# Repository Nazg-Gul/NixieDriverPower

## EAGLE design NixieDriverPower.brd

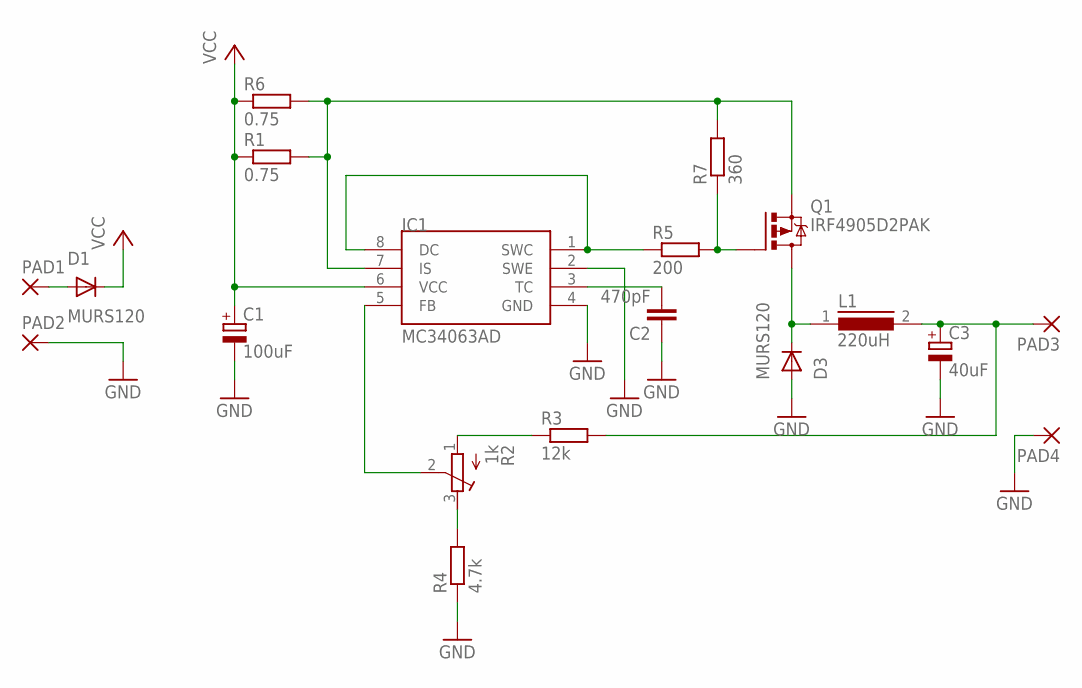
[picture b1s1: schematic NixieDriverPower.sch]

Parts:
C1: 100uF; D/7343-31R
C2: 470pF; C1206K
C3: 40uF; C/6032-28R
D1, D3: MURS120; DO214AA
IC1: MC34063AD; SOIC8
L1: 220uH; DR125
PAD1, PAD2, PAD3, PAD4: SMD5; SMD2,54-5,08
Q1: IRF4905D2PAK; D2PAK
R1, R6: 0.75; R1206
R2: 1k; RTRIM4G/J
R3: 12k; R1206
R4: 4.7k; R1206
R5: 200; R1206
R7: 360; R1206

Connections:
GND: C1.-, C2.1, C3.-, D3.A, IC1.2 (SWE), IC1.4 (GND), PAD2.1, PAD4.1, R4.1
unnamed: D3.C, L1.1, Q1.4 (D)
unnamed: C2.2, IC1.3 (TC)
unnamed: Q1.1 (G), R5.2, R7.1
unnamed: IC1.7 (IS), Q1.3 (S), R1.2, R6.2, R7.2
unnamed: C3.+, L1.2, PAD3.1, R3.2
unnamed: IC1.5 (FB), R2.2 (S)
unnamed: R2.3 (E), R4.2
unnamed: R2.1 (A), R3.1
unnamed: IC1.1 (SWC), IC1.8 (DC), R5.1
unnamed: D1.A, PAD1.1
VCC: C1.+, D1.C, IC1.6 (VCC), R1.1, R6.1

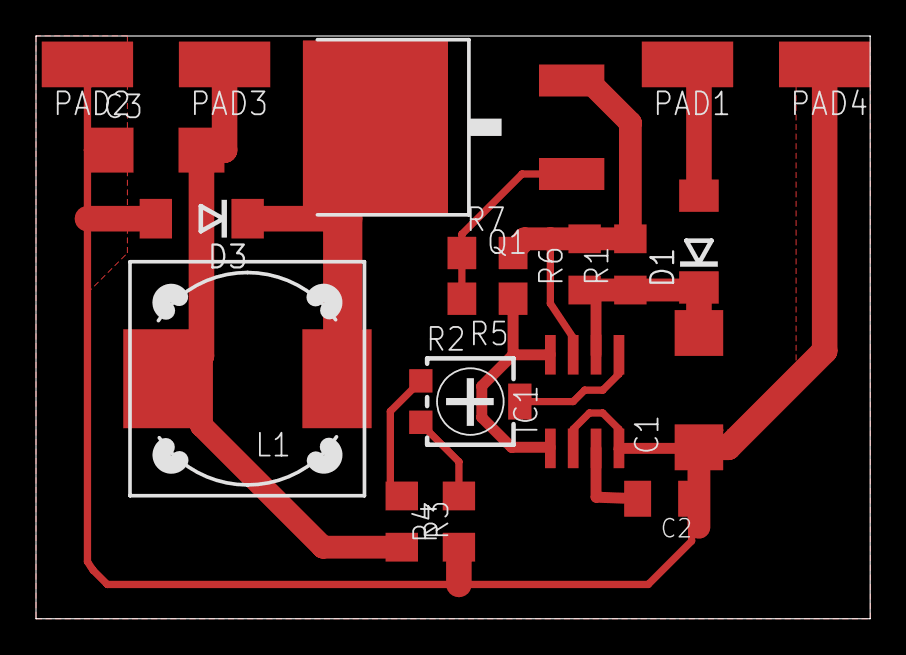
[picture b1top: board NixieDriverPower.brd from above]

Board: 2 copper layers, 46.3 x 32.4 mm, 19 parts (0 on the bottom side), 12 nets.

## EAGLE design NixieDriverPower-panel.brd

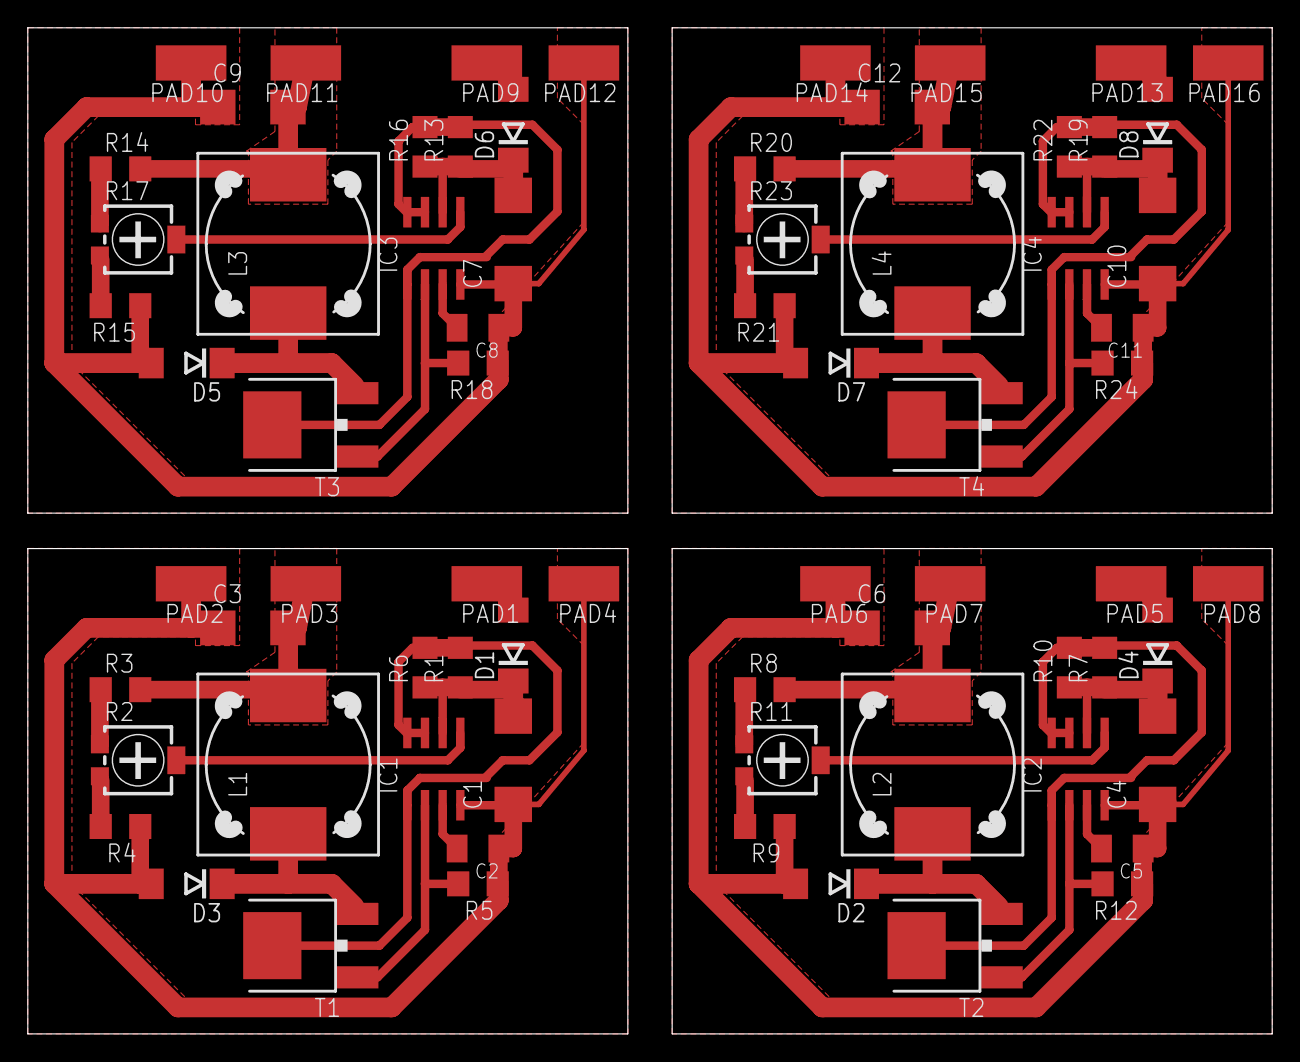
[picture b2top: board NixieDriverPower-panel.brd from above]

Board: 2 copper layers, 89.5 x 72.4 mm, 72 parts (0 on the bottom side), 44 nets.

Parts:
C1, C4, C7, C10: 100uF; D/7343-31R
C2, C5, C8, C11: 470pF; C1206K
C3, C6, C9, C12: 40uF; C/6032-28R
D1, D2, D3, D4, D5, D6, D7, D8: MURS120; DO214AA
IC1, IC2, IC3, IC4: MC34063AD; SOIC8
L1, L2, L3, L4: 220uH; DR125
PAD1, PAD2, PAD3, PAD4, PAD5, PAD6, PAD7, PAD8, PAD9, PAD10, PAD11, PAD12, PAD13, PAD14, PAD15, PAD16: SMD2,54-5,08
R1, R6, R7, R10, R13, R16, R19, R22: 0.75; R1206
R2, R11, R17, R23: 1k; RTRIM4G/J
R3, R8, R14, R20: 12k; R1206
R4, R9, R15, R21: 4.7k; R1206
R5, R12, R18, R24: 1.5k; R1206
T1, T2, T3, T4: MJD31; DPAK

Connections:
GND: C1.-, C2.1, C3.-, D3.A, IC1.4, PAD2.1, PAD4.1, R4.1, R5.1
GND1: C4.-, C5.1, C6.-, D2.A, IC2.4, PAD6.1, PAD8.1, R9.1, R12.1
GND2: C7.-, C8.1, C9.-, D5.A, IC3.4, PAD10.1, PAD12.1, R15.1, R18.1
GND3: C10.-, C11.1, C12.-, D7.A, IC4.4, PAD14.1, PAD16.1, R21.1, R24.1
unnamed: D3.C, L1.1, T1.3
unnamed: C2.2, IC1.3
unnamed: IC1.1, IC1.7, IC1.8, R1.2, R6.2, T1.4
unnamed: IC1.2, R5.2, T1.1
unnamed: IC2.1, IC2.7, IC2.8, R7.2, R10.2, T2.4
unnamed: C3.+, L1.2, PAD3.1, R3.2
unnamed: IC1.5, R2.2
unnamed: C5.2, IC2.3
unnamed: R2.1, R3.1
unnamed: R2.3, R4.2
unnamed: IC2.5, R11.2
unnamed: D1.A, PAD1.1
unnamed: C6.+, L2.2, PAD7.1, R8.2
unnamed: R8.1, R11.1
unnamed: R9.2, R11.3
unnamed: D4.A, PAD5.1
unnamed: IC2.2, R12.2, T2.1
unnamed: D2.C, L2.1, T2.3
unnamed: IC3.1, IC3.7, IC3.8, R13.2, R16.2, T3.4
unnamed: C8.2, IC3.3
unnamed: IC3.5, R17.2
unnamed: C9.+, L3.2, PAD11.1, R14.2
unnamed: R14.1, R17.1
unnamed: R15.2, R17.3
unnamed: D6.A, PAD9.1
unnamed: IC3.2, R18.2, T3.1
unnamed: D5.C, L3.1, T3.3
unnamed: IC4.1, IC4.7, IC4.8, R19.2, R22.2, T4.4
unnamed: C11.2, IC4.3
unnamed: IC4.5, R23.2
unnamed: C12.+, L4.2, PAD15.1, R20.2
unnamed: R20.1, R23.1
unnamed: R21.2, R23.3
unnamed: D8.A, PAD13.1
unnamed: IC4.2, R24.2, T4.1
unnamed: D7.C, L4.1, T4.3
VCC: C1.+, D1.C, IC1.6, R1.1, R6.1
VCC1: C4.+, D4.C, IC2.6, R7.1, R10.1
VCC2: C7.+, D6.C, IC3.6, R13.1, R16.1
VCC3: C10.+, D8.C, IC4.6, R19.1, R22.1

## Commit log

2017-01-21 Initial commit of Rev.A
2017-01-21 Commit of the current version
